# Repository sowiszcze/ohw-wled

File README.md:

# OHW-WLED - an OpenHardware project for a [WLED](https://github.com/Aircoookie/WLED) host PCB

> [!WARNING]
> This project (as is its owner) is really immature! Use it at your own risk!

This project aims to tackle an issue of mine, where I couldn't find a PCB design for ESP μC hosting WLED that suited my needs:
- Take in 5V DC power and output 5V logic
- Allow the use of all WLED's hardware features (through DIY extensions/modules)
- Be an Open Source Hardware project

I'm not saying there is no project like that, I just wasn't able to find one. As I was making it, I thought sharing the design could benefit someone or even (crazy thought, I know!) improve somebody's life, hence this repository.

Please be considerate of the license this project is shared on.

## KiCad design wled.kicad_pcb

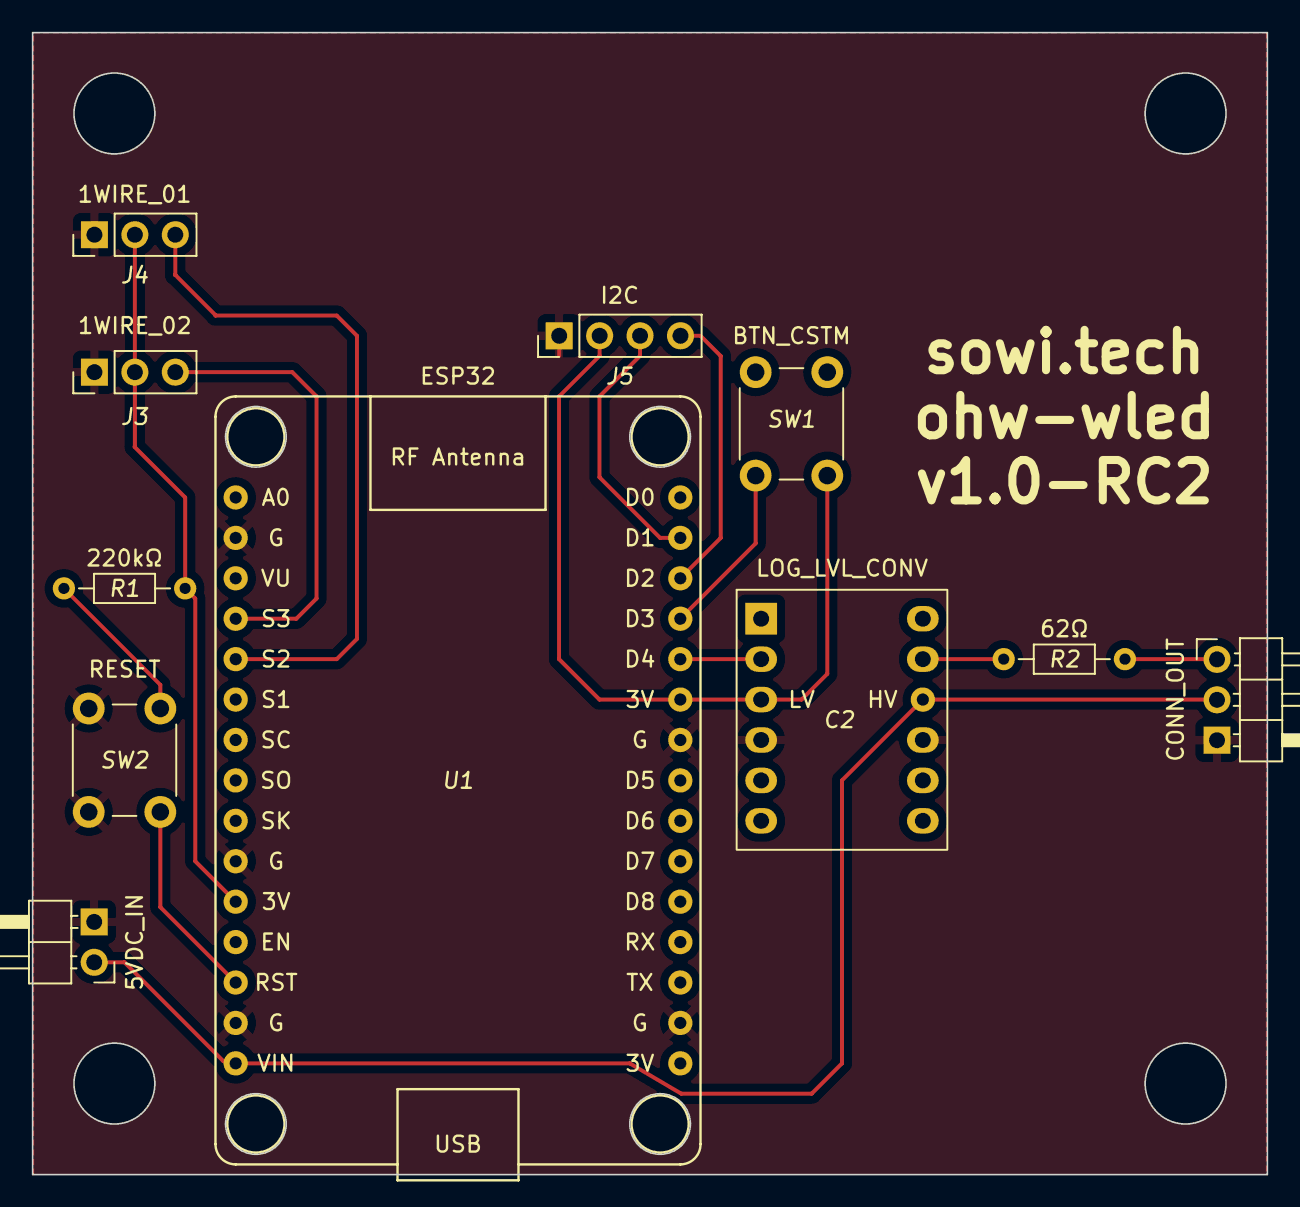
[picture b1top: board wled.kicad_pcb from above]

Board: 2 copper layers, 77.6 x 71.8 mm, 11 parts (0 on the bottom side), 12 nets.

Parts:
C2: Logic_level_converter; Logic_Level_Converter
J0: PinHeader_1x02_P2.54mm_Horizontal
J1: PinHeader_1x03_P2.54mm_Horizontal
J3: 1Wire_output_02; PinHeader_1x03_P2.54mm_Vertical
J4: 1Wire_output_01; PinHeader_1x03_P2.54mm_Vertical
J5: I2C_output_01; PinHeader_1x04_P2.54mm_Vertical
R1: 220kΩ; R_Axial_DIN0204_L3.6mm_D1.6mm_P7.62mm_Horizontal
R2: 62Ω; R_Axial_DIN0204_L3.6mm_D1.6mm_P7.62mm_Horizontal
SW1, SW2: SW_Push; SW_PUSH_6mm
U1: NodeMCU_1.0_(ESP-12E); NodeMCU1.0(12-E)

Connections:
1WIRE_01: J4.3, U1.5 (SD2(GPIO9))
1WIRE_02: J3.3, U1.4 (SD3(GPIO10))
3V3DC: C2.3 (LV), J3.2, J4.2, J5.2, R1.2, SW1.1, U1.11 (3.3V), U1.25 (3.3V)
5VDC: C2.9 (HV), J0.2, J1.2, U1.15 (VIN)
BTN_DATA: SW1.2, U1.27 (D3(GPIO0))
GND: C2.4 (GND), C2.10 (GND), J0.1, J1.1, J3.1, J4.1, J5.1, SW2.1, U1.2 (RSV), U1.10 (GND), U1.14 (GND), U1.17 (GND), U1.24 (GND)
I2C_SCL: J5.3, U1.29 (D1(GPIO5))
I2C_SDA: J5.4, U1.28 (D2(GPIO4))
RST_PUP: R1.1, SW2.2, U1.13 (RST)
SIG_OUT_3V3DC: C2.2 (LV2), U1.26 (D4(GPIO2))
SIG_OUT_5VDC: J1.3, R2.2
SIG_OUT_RAW: C2.8 (HV2), R2.1

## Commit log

2023-09-03 Create .gitignore
    KiCad flavour
2023-09-03 feat: Initial design
2023-09-03 feat: .gitignore include more production files
2023-09-03 feat: Updated PCB design
    This is a Release Candidate version of the board. It still has some issues, and they will be fixed in the next commit
2023-09-05 feat: Migrated project to KiCad 7.0
2023-10-12 feat: Extend .gitignore
2023-10-12 feat!: Second iteration of the board (one-sided)
